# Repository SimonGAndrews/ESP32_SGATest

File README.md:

# ESP32 Espruino Hardware Test Harnesses

This repository designs, documents, builds, and exercises Espruino and ESP32-family hardware
test harnesses for Espruino port validation.

It is both a hardware-design repo and a test/debug evidence base. The harnesses
are intended to exercise Espruino's user-facing APIs on real Espruino and ESP32-family
targets, especially where those APIs drive the low-level target-port layer and
its `jshardware` implementation.

The test strategy is to break the harness family into reusable physical test
blocks, then use those blocks as controlled hardware contexts for functional
API validation. So the harness wiring is an enabling condition, while the main
goal is to show that the Espruino MCU port behaves correctly when GPIO, timers,
buses, serial ports, and timing-sensitive protocols are used through realistic
hardware feedback paths.

## Purpose

The practical goal is to build repeatable Espruino and ESP32-family Espruino hardware
harnesses, run target-port validation tests against them, and preserve enough
design/debug context that hardware faults, firmware regressions, and test-runner
behaviour are documented.

The design principles are:

- keep the logical test blocks common across all targets
- adapt those blocks to each board through target-specific pin allocation,
  selectors, and wiring fanout
- build shared functional tests around Espruino API behaviour, not just around
  per-target wiring checks
- record the physical mode and firmware/test evidence well enough that future
  runs are comparable

## Project Progression

The work in this repository has progressed through these stages:

1. Developed the first ESP32-C3-DevKitC-02 hardware harness around the common
   Espruino test blocks.
2. Brought up the C3 harness with IDF4-based Espruino builds and validated the
   initial GPIO, analog, bus, and OneWire test paths.
3. Compared C3 IDF4 and IDF5 behaviour and captured IDF5 regression evidence,
   especially around `digitalPulse`.
4. Investigated C3-specific failures using comparison hardware and reference
   targets, separating harness wiring questions from firmware timing issues.
5. Resolved the major ESP32 OneWire instability as a targeted firmware timing
   issue while preserving the evidence and rationale in `docs/investigations/`.
6. Started the classic ESP32 harness generation, using the Olimex
   ESP32-DevKit-LiPo Rev.D / ESP32-WROOM-32E-style pinout as the practical
   DevKitC-compatible target for `ESP32_V1`.
7. Designed the ESP32 DevKitC V4 / `ESP32_V1` harness and PCB construction
   guide, ready for wirewrap build and bring-up.
8. Completed wirewrap builds for both the ESP32-C3 and classic ESP32 harnesses
   and added board photos under `Hardware/`.
9. Completed scripted wiring checks for the current harness blocks, including
   GPIO, analog/PWM, SPI, I2C, OneWire, DS2413, UART crosslink, and external
   connector paths where fitted.
10. Defined the shared REPL functional-test design, with JavaScript-owned
    target presets, Python-owned runner/parsing, and structured machine-readable
    output.
11. Proved the first shared functional block (`gpio_block1`) end to end across
    both current family targets on IDF4 firmware, using the same logical test
    files unchanged.
12. Started the V2 prototype implementation in `KICAD/V2/`, created curated
    target libraries, and adopted removable target daughter boards as the
    target-specific adaptation boundary.

## Current Targets

### ESP32-C3-DevKitC-02

The ESP32-C3 harness is built and has already been used for bring-up, scripted
wiring checks, and firmware debugging.

Important C3-specific features include:

- native USB Serial/JTAG on `D18` / `D19`
- UART0 on `D20` / `D21` reserved by default for board USB-UART REPL/flashing
- selector-heavy GPIO allocation due to the smaller available pin budget
- UART0/UART1 crosslink provisions that use native USB Serial/JTAG as the
  runner path; the DevKitC-02 onboard CP2102N TX must be isolated before its
  `D20` UART0 RX path can be used as the second crosslink direction

KiCad project:

```text
KICAD/V1/ESP32_C3_v1/
```

### Classic ESP32 DevKitC V4 / ESP32_V1

The classic ESP32 DevKitC V4 harness is now built and has completed its first
scripted wiring-check phase. The practical target is the Olimex
ESP32-DevKit-LiPo Rev.D. Olimex describe this board as pin-to-pin comparable
with the Espressif ESP32-CoreBoard
(`ESP32-DevKitC`), while adding LiPo charging and battery-powered operation.
The selected Rev.D hardware uses the classic ESP32 / ESP32-WROOM-32E-class
module family.

The harness uses a KiCad PCB design as a placement/silkscreen construction
guide rather than as a routed copper PCB.

Important ESP32_V1-specific features include:

- UART0 on `D1` / `D3` reserved for board USB-UART REPL/flashing/control
- UART1/UART2 crosslink for serial testing
- mostly fixed wiring because the classic ESP32 has more available GPIO
- selected sharing for `D35`, `D33`, and `D26`
- DS2413 removable OneWire GPIO breakout support

KiCad project:

```text
KICAD/V1/ESP32_V1/
```

## Common Harness Blocks

The harness family reuses the same logical test blocks wherever possible:

- GPIO loopbacks for `digitalWrite`, `digitalRead`, `pinMode`, `setWatch`, and
  `digitalPulse`
- PWM-to-ADC feedback
- SPI validation through MCP3008, with optional shared-bus flash device
- I2C validation through MCP23008, with feedback and interrupt paths
- OneWire validation through two DS18B20 devices
- OneWire GPIO validation through a DS2413 breakout
- UART/Serial crosslink tests
- reset/boot/automation provisions

Tests and documentation use Espruino `Dxx` pin names, matching GPIO numbers.

## Functional REPL Tests

The authoritative shared functional tests live under `tests/repl/`.

These tests are designed to:

- stay directly usable in the Espruino REPL or Web IDE
- keep target-specific pin and mode maps visible inside the JavaScript file
- emit structured output that a Python runner can parse unchanged
- validate Espruino API behaviour within the physical harness block that makes
  that behaviour observable

The current reference design for this test model is:

- `docs/design/repl-test-suite-design.md`

The first proven shared block is `tests/repl/gpio_block1/`, which currently
covers:

- `pinMode`
- `digitalWrite`
- `digitalRead`
- `setWatch`
- `digitalPulse`
- `shiftOut`

## Repository Map

```text
AGENTS.md                  Codex/new-thread operating notes
docs/                      Wiring specs, handoffs, investigation notes
tools/                     Python/REPL test utilities and wiring-test runners
KICAD/                     V1 and V2 schematic/PCB projects and local libraries
Hardware/                  Hardware reference material
tests/repl/                Portable community-facing REPL test scripts
```

Key starting documents:

- `AGENTS.md`
- `docs/handoff/2026-09-04-idf5-classic-validation-status.md` for the
  post-IDF5-merge ESP32 master sanity run and its historical evidence
- `docs/handoff/2026-06-25-esp32-family-tests.md`
- `docs/design/common-harness-design-and-blocks.md`
- `docs/design/repl-test-suite-design.md`
- `docs/design/harness-modes.md`
- `docs/targets/esp32-c3-devkitc-02/wiring.md`
- `docs/targets/esp32-devkitc-v4/wiring.md`

Useful external references:

- Olimex ESP32-DevKit-LiPo open-source hardware page:
  <https://www.olimex.com/Products/IoT/ESP32/ESP32-DevKit-LiPo/open-source-hardware>

## Test And Debug Context

The repo preserves the history and reasoning from real Espruino ESP32 testing,
including:

- REPL bring-up process
- C3 harness block tests
- OneWire investigation and final timing-fix shape
- IDF4 vs IDF5 comparisons
- `digitalPulse` regression evidence
- watch/debounce investigation notes
- scripted REPL test tools

Important conclusions from prior work:

- ESP32 OneWire instability was narrowed to firmware-side timing behaviour, not
  simply bad harness wiring.
- The accepted OneWire fix shape is a localized ESP32 timing guard inside
  `src/jswrap_onewire.c`, not a broad/global interrupt semantic change.
- `digitalPulse` was a separate ESP32-C3 IDF5 regression signal after basic
  `digitalWrite`, `digitalRead`, and `setWatch` paths had been shown to work.
- Selector/jumper state is part of every test precondition and must be recorded
  with test evidence.

## Current Active Work

The current hardware state is that both harness boards are built and their
initial scripted wiring-check coverage is in place.

The shared functional suite now covers GPIO, watches and pulses, analogue and
PWM paths, I2C, SPI, OneWire, UART and paired Wi-Fi/BLE behaviour where the V1
harness and peer hardware support them. It has been used for repeatable classic
ESP32 master-versus-IDF5 comparisons and for targeted ESP32-C3 evidence. The
older IDF4 results remain useful comparators rather than the current endpoint.

The expedited ESP32 IDF5 validation supplied build and V1 regression evidence
that informed Gordon Williams' decision to merge the official `IDF5` branch
into Espruino `master` at `5d79af218`. The same-source post-merge sanity check
of `BOARD=ESP32` and `BOARD=ESP32_IDF5` is complete. Further defects have
returned to normal Espruino-master investigation; the first follow-up was UART
driver-lifecycle pull request `#2742`, merged as `e6a3fe089`. Its family-wide
revision has compile coverage across seven ESP32 board definitions and runtime
coverage on classic ESP32, ESP32-C3 and ESP32-S3 hardware. See
`docs/handoff/2026-09-04-idf5-classic-validation-status.md`.

This work continues block-by-block expansion of the shared functional suite,
with the aim of:

- exercising Espruino APIs more fully across the common harness blocks
- preserving the existing per-target wiring checks as hardware-regression
  references
- retaining useful legacy and IDF4 comparators for anomaly attribution
- applying the same shared functional coverage to both ESP32 board targets in
  current master
- keeping new tests portable to the future V2 target-map layer

V2 architecture and KiCad implementation remain active and can continue in
parallel with normal master regression work. The current V2 return point is
commit `c70e50c`, which established the Rev-A daughter-board foundations. See
`docs/design/V2Harness/README.md` for the V2 entry point.

Routine V1 hardware development and prototyping have stopped. The completed V1
harnesses remain the stable bench platforms for runner development, regression
testing and firmware evidence.

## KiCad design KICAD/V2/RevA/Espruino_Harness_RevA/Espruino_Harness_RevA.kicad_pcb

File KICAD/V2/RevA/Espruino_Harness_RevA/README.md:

# Espruino Harness V2 Rev A

This is the fresh KiCad 9 project for the V2 Rev-A engineering-validation
harness.

The production hierarchy deliberately uses five pages:

1. `Espruino_Harness_RevA.kicad_sch` — the main A2 system page containing
   power, Rack Control, target control, the Target Interface and the
   hierarchical connections between the implementation pages.
2. `standard_test_blocks.kicad_sch` — one A2 page containing all accepted
   Standard Test Blocks as clearly labelled circuit sections.
3. `prototype_daughter_board.kicad_sch` — one A3 page containing the flexible
   wire-wrap daughter-board implementation.
4. `routing_control.kicad_sch` — one A3 page containing the Routing Fabric,
   both routing-control MCP23017s and the fixed direct-I2C isolation.
5. `power_control.kicad_sch` — one A2 page containing operating-mode
   selection, the 3.3 V rail selection and Test Block power control, and the
   target 5 V switch and two-range current monitor.

The main page is the visual integration view. Keep important supply, control,
routing and Target Interface relationships visible there. Diagnostic links,
isolation components and test points remain beside the circuits that own them.

## Draft workbench

`draft_workbench.kicad_sch` is an A3 standalone schematic for candidate
circuits and alternative implementations. It uses the project-local libraries
but is deliberately not referenced by the production hierarchy.

The workbench is therefore absent from production hierarchy exports, ERC,
netlists and BOMs. Validate it independently while drafting. When a circuit is
accepted:

1. copy it into its production-sheet location
2. check and, where necessary, re-annotate its references
3. inspect copied labels, power symbols and no-connect markers
4. run ERC and export the netlist from the production root schematic
5. compare the resulting connections with the governing specification

Do not treat the presence of a circuit on the workbench as design acceptance.

Use the project-local libraries described in `LIBRARY_PROVENANCE.md`. Bring
assets across from the exploratory project only after individual review.

The Rev-A verification scaffold is under `verification/`. Production ERC and
netlist evidence must be generated from the root schematic, not from an
individual hierarchical sheet.

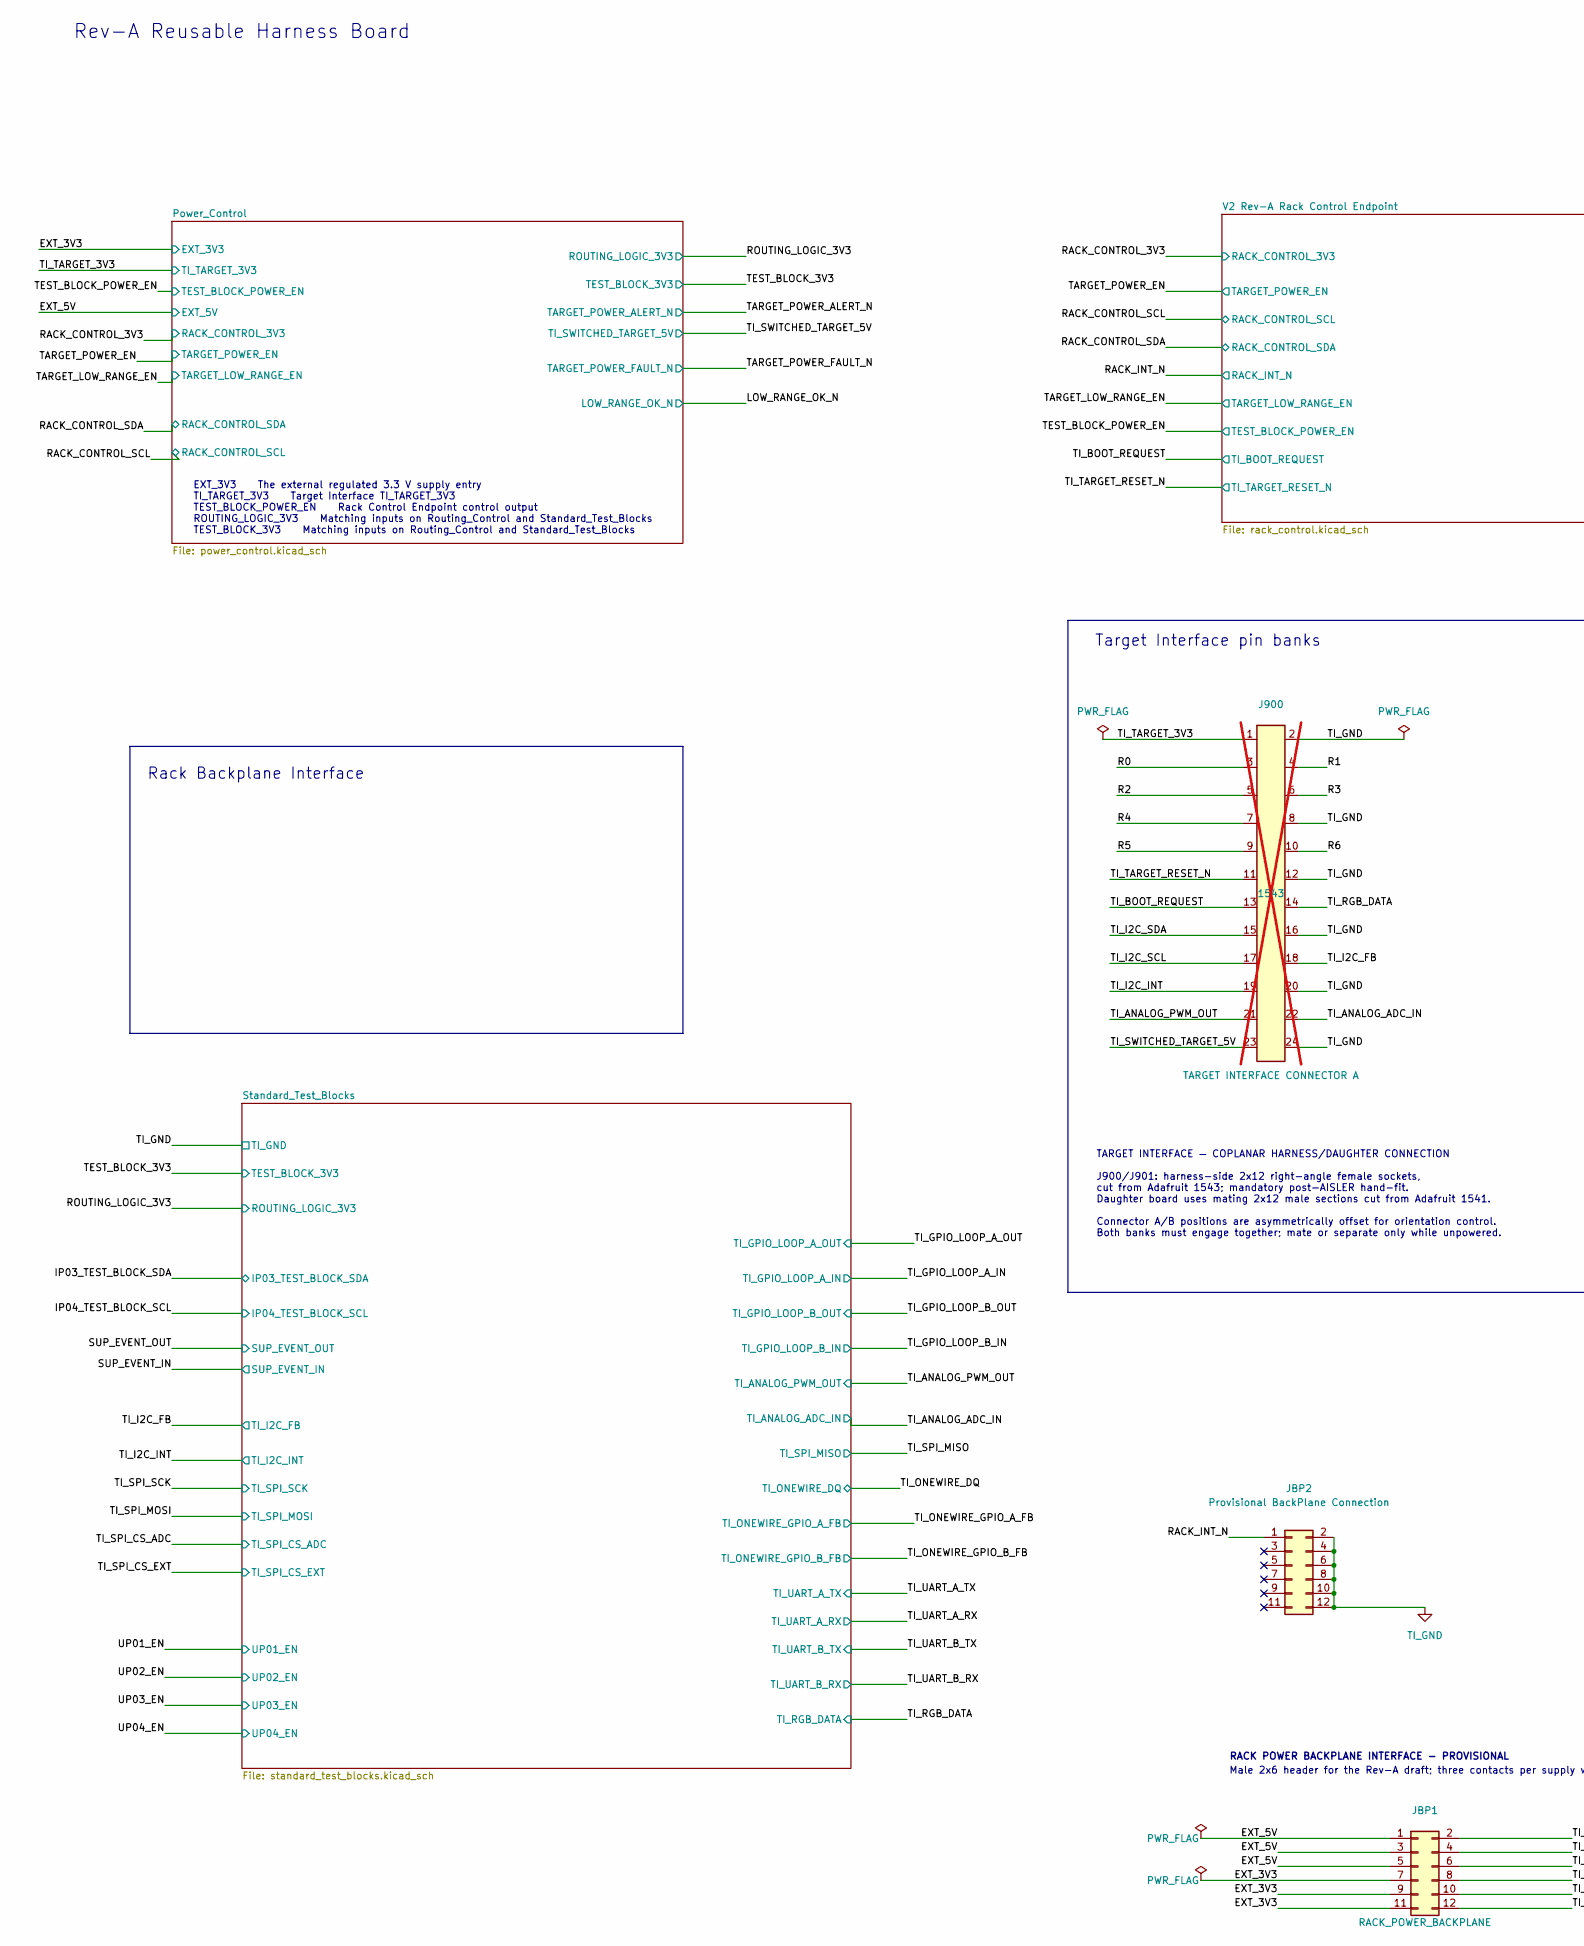
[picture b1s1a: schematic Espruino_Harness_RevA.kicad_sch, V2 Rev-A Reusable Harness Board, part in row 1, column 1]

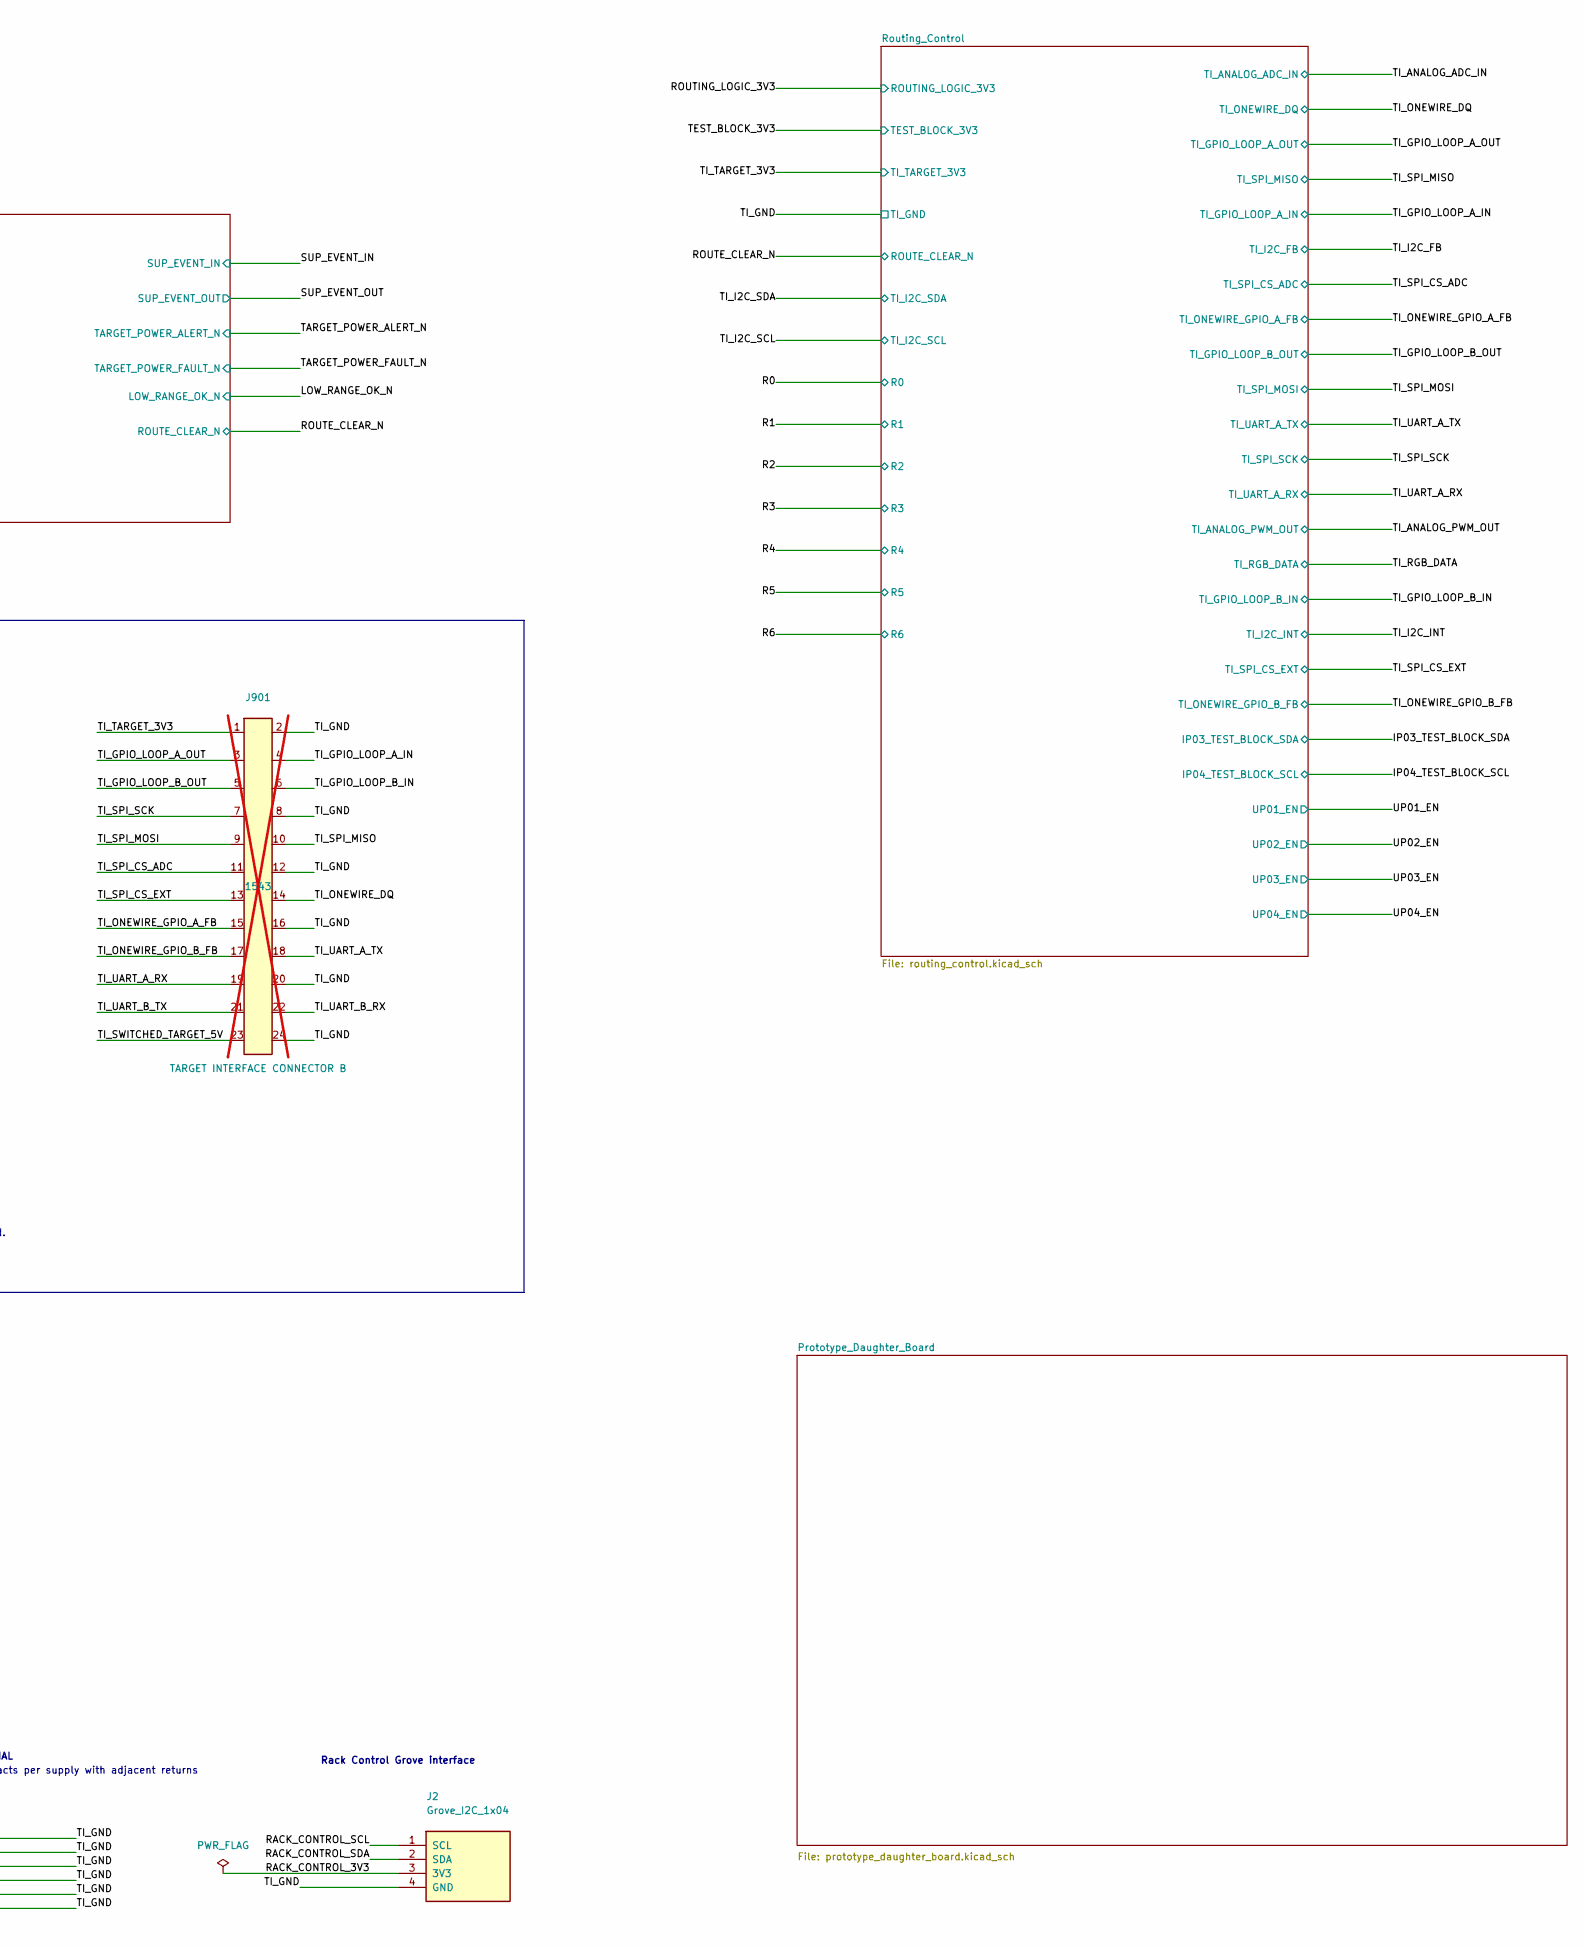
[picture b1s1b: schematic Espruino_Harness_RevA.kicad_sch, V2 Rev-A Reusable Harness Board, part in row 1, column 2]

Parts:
J2: Grove_I2C_1x04
J900: TARGET INTERFACE CONNECTOR A; TargetInterface_2x12_P2.54mm_RA_Female_Adafruit1543_Harness; MPN 1543; not fitted
J901: TARGET INTERFACE CONNECTOR B; TargetInterface_2x12_P2.54mm_RA_Female_Adafruit1543_Harness; MPN 1543; not fitted
JBP1: RACK_POWER_BACKPLANE; PinHeader_2x06_P2.54mm_Vertical
JBP2: Provisional BackPlane Connection

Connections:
/EXT_3V3: JBP1.7, JBP1.9, JBP1.11; also elsewhere on the board
/EXT_5V: JBP1.1, JBP1.3, JBP1.5; also elsewhere on the board
/R0: J900.3 (Contact_03); also elsewhere on the board
/R1: J900.4 (Contact_04); also elsewhere on the board
/R2: J900.5 (Contact_05); also elsewhere on the board
/R3: J900.6 (Contact_06); also elsewhere on the board
/R4: J900.7 (Contact_07); also elsewhere on the board
/R5: J900.9 (Contact_09); also elsewhere on the board
/R6: J900.10 (Contact_10); also elsewhere on the board
/TI_ANALOG_ADC_IN: J900.22 (Contact_22); also elsewhere on the board
/TI_ANALOG_PWM_OUT: J900.21 (Contact_21); also elsewhere on the board
/TI_BOOT_REQUEST: J900.13 (Contact_13); also elsewhere on the board
/TI_GPIO_LOOP_A_IN: J901.4 (Contact_04); also elsewhere on the board
/TI_GPIO_LOOP_A_OUT: J901.3 (Contact_03); also elsewhere on the board
/TI_GPIO_LOOP_B_IN: J901.6 (Contact_06); also elsewhere on the board
/TI_GPIO_LOOP_B_OUT: J901.5 (Contact_05); also elsewhere on the board
/TI_I2C_FB: J900.18 (Contact_18); also elsewhere on the board
/TI_I2C_INT: J900.19 (Contact_19); also elsewhere on the board
/TI_I2C_SCL: J900.17 (Contact_17); also elsewhere on the board
/TI_I2C_SDA: J900.15 (Contact_15); also elsewhere on the board
/TI_ONEWIRE_DQ: J901.14 (Contact_14); also elsewhere on the board
/TI_ONEWIRE_GPIO_A_FB: J901.15 (Contact_15); also elsewhere on the board
/TI_ONEWIRE_GPIO_B_FB: J901.17 (Contact_17); also elsewhere on the board
/TI_RGB_DATA: J900.14 (Contact_14); also elsewhere on the board
/TI_SPI_CS_ADC: J901.11 (Contact_11); also elsewhere on the board
/TI_SPI_CS_EXT: J901.13 (Contact_13); also elsewhere on the board
/TI_SPI_MISO: J901.10 (Contact_10); also elsewhere on the board
/TI_SPI_MOSI: J901.9 (Contact_09); also elsewhere on the board
/TI_SPI_SCK: J901.7 (Contact_07); also elsewhere on the board
/TI_SWITCHED_TARGET_5V: J900.23 (Contact_23), J901.23 (Contact_23); also elsewhere on the board
/TI_TARGET_3V3: J900.1 (Contact_01), J901.1 (Contact_01); also elsewhere on the board
/TI_TARGET_RESET_N: J900.11 (Contact_11); also elsewhere on the board
/TI_UART_A_RX: J901.19 (Contact_19); also elsewhere on the board
/TI_UART_A_TX: J901.18 (Contact_18); also elsewhere on the board
/TI_UART_B_RX: J901.22 (Contact_22); also elsewhere on the board
/TI_UART_B_TX: J901.21 (Contact_21); also elsewhere on the board
unnamed: JBP2.2, JBP2.4, JBP2.6, JBP2.8, JBP2.10, JBP2.12
TI_GND: J2.4 (GND), J900.2 (Contact_02), J900.8 (Contact_08), J900.12 (Contact_12), J900.16 (Contact_16), J900.20 (Contact_20), J900.24 (Contact_24), J901.2 (Contact_02), J901.8 (Contact_08), J901.12 (Contact_12), J901.16 (Contact_16), J901.20 (Contact_20), J901.24 (Contact_24), JBP1.2, JBP1.4, JBP1.6, JBP1.8, JBP1.10, JBP1.12; also elsewhere on the board

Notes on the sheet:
Male 2x6 header for the Rev-A draft; three contacts per supply with adjacent returns
Rack Control Grove interface
TARGET INTERFACE — COPLANAR HARNESS/DAUGHTER CONNECTION J900/J901: harness-side 2x12 right-angle female sockets, cut from Adafruit 1543; mandatory post-AISLER hand-fit. Daughter board uses mating 2x12 male sections cut from Adafruit 1541. Connector A/B positions are asymmetrically offset for orient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
RACK POWER BACKPLANE INTERFACE - PROVISIONAL
Target Interface pin banks
Rev-A Reusable Harness Board
EXT_3V3 The external regulated 3.3 V supply entry TI_TARGET_3V3 Target Interface TI_TARGET_3V3 TEST_BLOCK_POWER_EN Rack Control Endpoint control output ROUTING_LOGIC_3V3 Matching inputs on Routing_Control and Standard_Test_Blocks TEST_BLOCK_3V3 Matching inputs on Routing_Control and Standard_Test_B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
Rack Backplane Interface

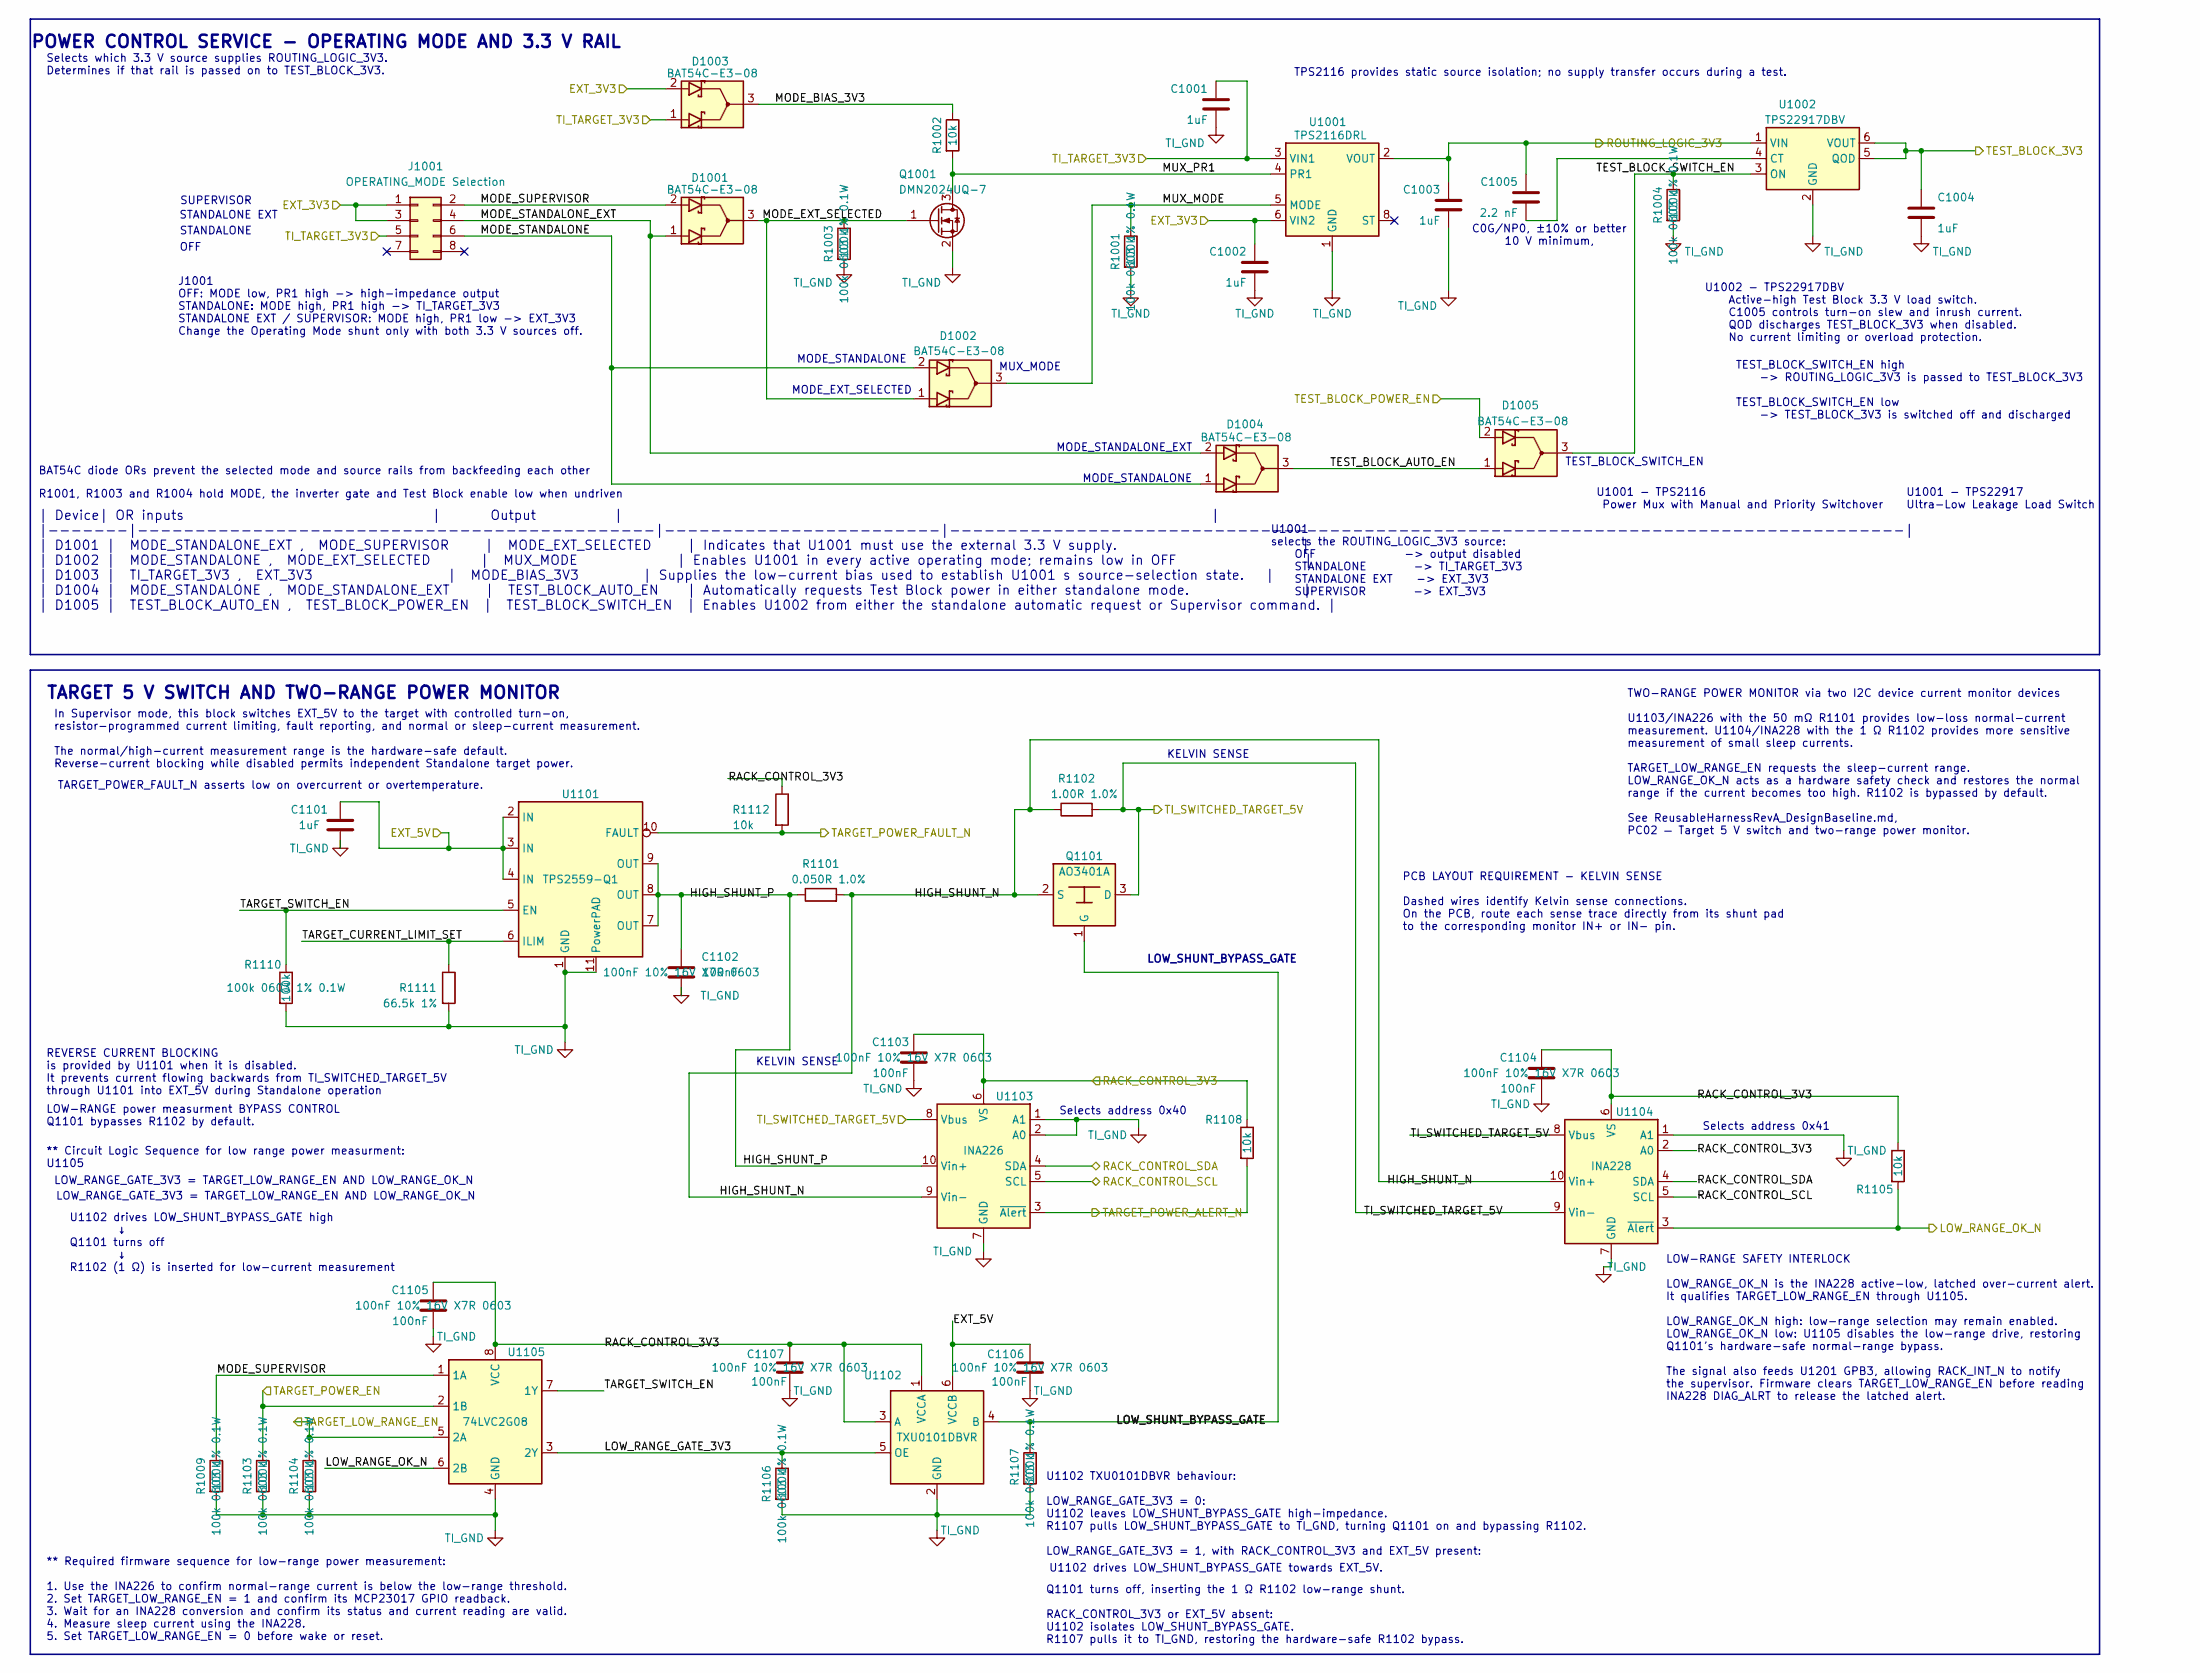
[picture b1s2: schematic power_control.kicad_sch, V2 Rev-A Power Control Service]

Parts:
C1001, C1002, C1003, C1004, C1101: 1uF; C_0603_1608Metric
C1005: 2.2 nF; C_0603_1608Metric
C1102, C1103, C1104, C1105, C1106, C1107: 100nF; C_0603_1608Metric
D1001, D1002, D1003, D1004, D1005: BAT54C-E3-08; SOT-23
J1001: OPERATING_MODE Selection; PinHeader_2x04_P2.54mm_Vertical
Q1001: DMN2024UQ-7; SOT-23
Q1101: AO3401A; SOT-23
R1001, R1003, R1004, R1009, R1103, R1104, R1106, R1107, R1110: 100k; R_0603_1608Metric
R1002, R1105, R1108, R1112: 10k; R_0603_1608Metric
R1101: 0.050R 1.0%; R_0603_1608Metric
R1102: 1.00R 1.0%; R_0603_1608Metric
R1111: 66.5k 1%; R_0603_1608Metric
U1001: TPS2116DRL; SOT-583-8
U1002: TPS22917DBV; SOT-23-6
U1101: TPS2559-Q1; TPS2559Q1_DRC0010K_VSON10_EP
U1102: TXU0101DBVR; SOT-23-6
U1103: INA226; VSSOP-10_3x3mm_P0.5mm
U1104: INA228; VSSOP-10_3x3mm_P0.5mm
U1105: 74LVC2G08; VSSOP-8_2.3x2mm_P0.5mm

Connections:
/EXT_3V3: C1002.2, D1003.2 (A2), J1001.1, J1001.3, U1001.6 (VIN2); also elsewhere on the board
/EXT_5V: C1101.1, C1106.1, U1101.2 (IN), U1101.3 (IN), U1101.4 (IN), U1102.6 (VCCB); also elsewhere on the board
/LOW_RANGE_OK_N: R1105.2, U1104.3 (~Alert), U1105.6 (2B); also elsewhere on the board
/Power_Control/HIGH_SHUNT_N: Q1101.2 (S), R1101.2, R1102.1, U1103.9 (Vin-), U1104.10 (Vin+)
/Power_Control/HIGH_SHUNT_P: C1102.1, R1101.1, U1101.7 (OUT), U1101.8 (OUT), U1101.9 (OUT), U1103.10 (Vin+)
/Power_Control/LOW_RANGE_GATE_3V3: R1106.1, U1102.5 (OE), U1105.3 (2Y)
/Power_Control/LOW_SHUNT_BYPASS_GATE: Q1101.1 (G), R1107.1, U1102.4 (B)
/Power_Control/MODE_BIAS_3V3: D1003.3 (K), R1002.1
/Power_Control/MODE_EXT_SELECTED: D1001.3 (K), D1002.1 (A1), Q1001.1 (G), R1003.1
/Power_Control/MODE_STANDALONE: D1002.2 (A2), D1004.1 (A1), J1001.6
/Power_Control/MODE_STANDALONE_EXT: D1001.1 (A1), D1004.2 (A2), J1001.4
/Power_Control/MODE_SUPERVISOR: D1001.2 (A2), J1001.2, R1009.1, U1105.1 (1A)
/Power_Control/MUX_MODE: D1002.3 (K), R1001.1, U1001.5 (MODE)
/Power_Control/MUX_PR1: Q1001.3 (D), R1002.2, U1001.4 (PR1)
/Power_Control/TARGET_CURRENT_LIMIT_SET: R1111.1, U1101.6 (ILIM)
/Power_Control/TARGET_SWITCH_EN: R1110.1, U1101.5 (EN), U1105.7 (1Y)
/Power_Control/TEST_BLOCK_AUTO_EN: D1004.3 (K), D1005.1 (A1)
/Power_Control/TEST_BLOCK_SWITCH_EN: D1005.3 (K), R1004.1, U1002.3 (ON)
/RACK_CONTROL_3V3: C1103.1, C1104.1, C1105.1, C1107.1, R1105.1, R1108.1, R1112.1, U1102.1 (VCCA), U1102.3 (A), U1103.6 (VS), U1104.2 (A0), U1104.6 (VS), U1105.8 (VCC); also elsewhere on the board
/RACK_CONTROL_SCL: U1103.5 (SCL), U1104.5 (SCL); also elsewhere on the board
/RACK_CONTROL_SDA: U1103.4 (SDA), U1104.4 (SDA); also elsewhere on the board
/ROUTING_LOGIC_3V3: C1003.2, C1005.2, U1001.2 (VOUT), U1001.7 (VOUT), U1002.1 (VIN); also elsewhere on the board
/TARGET_LOW_RANGE_EN: R1104.1, U1105.5 (2A); also elsewhere on the board
/TARGET_POWER_ALERT_N: R1108.2, U1103.3 (~Alert); also elsewhere on the board
/TARGET_POWER_EN: R1103.1, U1105.2 (1B); also elsewhere on the board
/TARGET_POWER_FAULT_N: R1112.2, U1101.10 (FAULT); also elsewhere on the board
/TEST_BLOCK_3V3: C1004.1, U1002.5 (QOD), U1002.6 (VOUT); also elsewhere on the board
/TEST_BLOCK_POWER_EN: D1005.2 (A2); also elsewhere on the board
/TI_SWITCHED_TARGET_5V: Q1101.3 (D), R1102.2, U1103.8 (Vbus), U1104.8 (Vbus), U1104.9 (Vin-); also elsewhere on the board
/TI_TARGET_3V3: C1001.2, D1003.1 (A1), J1001.5, U1001.3 (VIN1); also elsewhere on the board
unnamed: C1005.1, U1002.4 (CT)
TI_GND: C1001.1, C1002.1, C1003.1, C1004.2, C1101.2, C1102.2, C1103.2, C1104.2, C1105.2, C1106.2, C1107.2, Q1001.2 (S), R1001.2, R1003.2, R1004.2, R1009.2, R1103.2, R1104.2, R1106.2, R1107.2, R1110.2, R1111.2, U1001.1 (GND), U1002.2 (GND), U1101.1 (GND), U1101.11 (PowerPAD), U1102.2 (GND), U1103.1 (A1), U1103.2 (A0), U1103.7 (GND), U1104.1 (A1), U1104.7 (GND), U1105.4 (GND); also elsewhere on the board

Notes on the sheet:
U1102 TXU0101DBVR behaviour: LOW_RANGE_GATE_3V3 = 0: U1102 leaves LOW_SHUNT_BYPASS_GATE high-impedance. R1107 pulls LOW_SHUNT_BYPASS_GATE to TI_GND, turning Q1101 on and bypassing R1102. LOW_RANGE_GATE_3V3 = 1, with RACK_CONTROL_3V3 and EXT_5V present:
STANDALONE EXT
U1001 - TPS2116 Power Mux with Manual and Priority Switchover
KELVIN SENSE
STANDALONE
Selects address 0x41
LOW-RANGE power measurment BYPASS CONTROL Q1101 bypasses R1102 by default.
MUX_MODE
LOW_RANGE_GATE_3V3 = TARGET_LOW_RANGE_EN AND LOW_RANGE_OK_N
POWER CONTROL SERVICE - OPERATING MODE AND 3.3 V RAIL
** Circuit Logic Sequence for low range power measurment: U1105
MODE_STANDALONE_EXT
Selects which 3.3 V source supplies ROUTING_LOGIC_3V3. Determines if that rail is passed on to TEST_BLOCK_3V3.
TWO-RANGE POWER MONITOR via two I2C device current monitor devices U1103/INA226 with the 50 mΩ R1101 provides low-loss normal-current measurement. U1104/INA228 with the 1 Ω R1102 provides more sensitive measurement of small sleep currents. TARGET_LOW_RANGE_EN requests the sleep-current range. LOW_R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
U1102 drives LOW_SHUNT_BYPASS_GATE towards EXT_5V.
BAT54C diode ORs prevent the selected mode and source rails from backfeeding each other
TARGET_POWER_FAULT_N asserts low on overcurrent or overtemperature.
MODE_STANDALONE
U1002 - TPS22917DBV Active-high Test Block 3.3 V load switch. C1005 controls turn-on slew and inrush current. QOD discharges TEST_BLOCK_3V3 when disabled. No current limiting or overload protection.
OFF
Q1101 turns off, inserting the 1 Ω R1102 low-range shunt. RACK_CONTROL_3V3 or EXT_5V absent: U1102 isolates LOW_SHUNT_BYPASS_GATE. R1107 pulls it to TI_GND, restoring the hardware-safe R1102 bypass.
LOW_RANGE_GATE_3V3 = TARGET_LOW_RANGE_EN AND LOW_RANGE_OK_N
REVERSE CURRENT BLOCKING is provided by U1101 when it is disabled. It prevents current flowing backwards from TI_SWITCHED_TARGET_5V through U1101 into EXT_5V during Standalone operation
PCB LAYOUT REQUIREMENT - KELVIN SENSE Dashed wires identify Kelvin sense connections. On the PCB, route each sense trace directly from its shunt pad to the corresponding monitor IN+ or IN− pin.
TPS2116 provides static source isolation; no supply transfer occurs during a test.
J1001 OFF: MODE low, PR1 high -> high-impedance output STANDALONE: MODE high, PR1 high -> TI_TARGET_3V3 STANDALONE EXT / SUPERVISOR: MODE high, PR1 low -> EXT_3V3 Change the Operating Mode shunt only with both 3.3 V sources off.
SUPERVISOR
TARGET 5 V SWITCH AND TWO-RANGE POWER MONITOR
LOW_SHUNT_BYPASS_GATE
LOW-RANGE SAFETY INTERLOCK LOW_RANGE_OK_N is the INA228 active-low, latched over-current alert. It qualifies TARGET_LOW_RANGE_EN through U1105. LOW_RANGE_OK_N high: low-range selection may remain enabled. LOW_RANGE_OK_N low: U1105 disables the low-range drive, restoring Q1101’s hardware-safe normal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
TEST_BLOCK_SWITCH_EN high -> ROUTING_LOGIC_3V3 is passed to TEST_BLOCK_3V3 TEST_BLOCK_SWITCH_EN low -> TEST_BLOCK_3V3 is switched off and discharged
U1001 - TPS22917 Ultra-Low Leakage Load Switch
C0G/NP0, ±10% or better 10 V minimum,
TEST_BLOCK_SWITCH_EN
R1001, R1003 and R1004 hold MODE, the inverter gate and Test Block enable low when undriven
Selects address 0x40
MODE_EXT_SELECTED
| Device| OR inputs | Output | | |-------|---------------------------------------------|------------------------|-----------------------------------------------------------------------------------| | D1001 | MODE_STANDALONE_EXT , MODE_SUPERVISOR | MODE_EXT_SELECTED | Indicates that U1001 must use t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
** Required firmware sequence for low-range power measurement: 1. Use the INA226 to confirm normal-range current is below the low-range threshold. 2. Set TARGET_LOW_RANGE_EN = 1 and confirm its MCP23017 GPIO readback. 3. Wait for an INA228 conversion and confirm its status and current reading are v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
In Supervisor mode, this block switches EXT_5V to the target with controlled turn-on, resistor-programmed current limiting, fault reporting, and normal or sleep-current measurement. The normal/high-current measurement range is the hardware-safe default. Reverse-current blocking while disabled permi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
